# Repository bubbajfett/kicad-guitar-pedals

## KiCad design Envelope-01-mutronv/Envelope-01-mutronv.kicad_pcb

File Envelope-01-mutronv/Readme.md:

Envelope filter based on the Mutron V

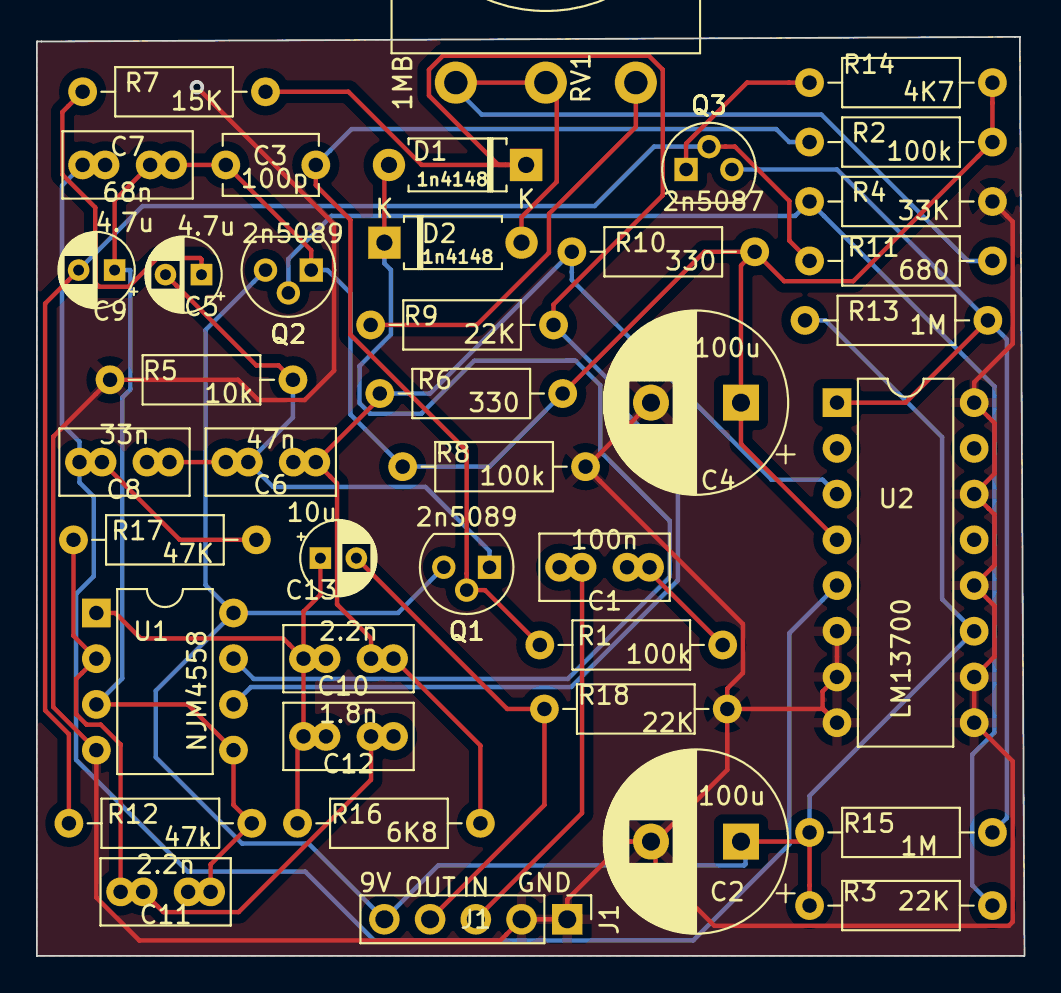
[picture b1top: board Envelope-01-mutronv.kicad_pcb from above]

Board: 2 copper layers, 54.9 x 51.1 mm, 40 parts (0 on the bottom side), 21 nets.

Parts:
C1: 100n; C_Rect_L7.0mm_W3.5mm_P2.50mm_P5.00mm
C2, C4: 100u; CP_Radial_D10.0mm_P5.00mm
C3: 100p; C_Disc_D5.1mm_W3.2mm_P5.00mm
C5, C9: 4.7u; CP_Radial_D4.0mm_P2.00mm
C6: 47n; C_Rect_L7.0mm_W3.5mm_P2.50mm_P5.00mm
C7: 68n; C_Rect_L7.0mm_W3.5mm_P2.50mm_P5.00mm
C8: 33n; C_Rect_L7.0mm_W3.5mm_P2.50mm_P5.00mm
C10, C11: 2.2n; C_Rect_L7.0mm_W3.5mm_P2.50mm_P5.00mm
C12: 1.8n; C_Rect_L7.0mm_W3.5mm_P2.50mm_P5.00mm
C13: 10u; CP_Radial_D4.0mm_P2.00mm
D1, D2: 1n4148; D_A-405_P7.62mm_Horizontal
J1: Conn_01x05; PinHeader_1x05_P2.54mm_Vertical
Q1, Q2: 2n5089; TO-92
Q3: 2n5087; TO-92
R1, R2, R8: 100k; R_Axial_DIN0207_L6.3mm_D2.5mm_P10.16mm_Horizontal
R3, R9, R18: 22K; R_Axial_DIN0207_L6.3mm_D2.5mm_P10.16mm_Horizontal
R4: 33K; R_Axial_DIN0207_L6.3mm_D2.5mm_P10.16mm_Horizontal
R5: 10k; R_Axial_DIN0207_L6.3mm_D2.5mm_P10.16mm_Horizontal
R6, R10: 330; R_Axial_DIN0207_L6.3mm_D2.5mm_P10.16mm_Horizontal
R7: 15K; R_Axial_DIN0207_L6.3mm_D2.5mm_P10.16mm_Horizontal
R11: 680; R_Axial_DIN0207_L6.3mm_D2.5mm_P10.16mm_Horizontal
R12: 47k; R_Axial_DIN0207_L6.3mm_D2.5mm_P10.16mm_Horizontal
R13, R15: 1M; R_Axial_DIN0207_L6.3mm_D2.5mm_P10.16mm_Horizontal
R14: 4K7; R_Axial_DIN0207_L6.3mm_D2.5mm_P10.16mm_Horizontal
R16: 6K8; R_Axial_DIN0207_L6.3mm_D2.5mm_P10.16mm_Horizontal
R17: 47K; R_Axial_DIN0207_L6.3mm_D2.5mm_P10.16mm_Horizontal
RV1: 1MB; Potentiometer_Omeg_PC16BU_Vertical
U1: NJM4558; DIP-8_W7.62mm
U2: LM13700; DIP-16_W7.62mm

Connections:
9v: C2.1, J1.5, Q1.3 (C), Q2.3 (C), R3.2, R13.2, R15.2, U1.8 (V+), U2.11 (V+)
GND: C2.2, C4.2, J1.1, J1.2, R4.1, R5.1, R8.1, R18.1, U1.4 (V-), U2.6 (V-), U2.7, U2.8, U2.9, U2.10, U2.12, U2.14 (+), U2.16
IN: C1.2, J1.3
unnamed: C1.1, R1.2
unnamed: C3.1, Q1.2 (B), R1.1, R2.2
unnamed: C5.1, R7.2
unnamed: C5.2, C6.2, C8.1, Q1.1 (E), R5.2
unnamed: C7.1, C8.2, R17.1, U2.5
unnamed: C9.2, Q3.2 (B), R11.2, R12.2
unnamed: C6.1, C10.1, R6.2, R10.2, R16.1, U2.3 (+)
unnamed: C10.2, C12.2, C13.1, R16.2, U1.1
unnamed: C11.2, C12.1, R17.2, U1.2 (-)
unnamed: D1.1 (K), R7.1, R9.1, U1.6 (-)
unnamed: D1.2 (A), D2.1 (K), U1.7
unnamed: Q2.2 (B), R3.1, R4.2
unnamed: Q3.1 (E), R14.2
unnamed: Q3.3 (C), R13.1, R15.1, U2.1
unnamed: R9.2, RV1.1
unnamed: D2.2 (A), R11.1, RV1.2, RV1.3
OUT: C13.2, J1.4, R18.2
VB: C3.2, C4.1, C7.2, C9.1, C11.1, Q2.1 (E), R2.1, R6.1, R8.2, R10.1, R12.1, R14.1, U1.3 (+), U1.5 (+), U2.4 (-)

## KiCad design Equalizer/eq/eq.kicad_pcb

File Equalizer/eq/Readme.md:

# eq

This is a 6-band equalizer based on a schematic in the PedalPCB site.
This is really a nice pedal to have on the board, and I like it in the
end of the chain, but not sure that is correct.   

All registered trademarks are owned by their respective owners.

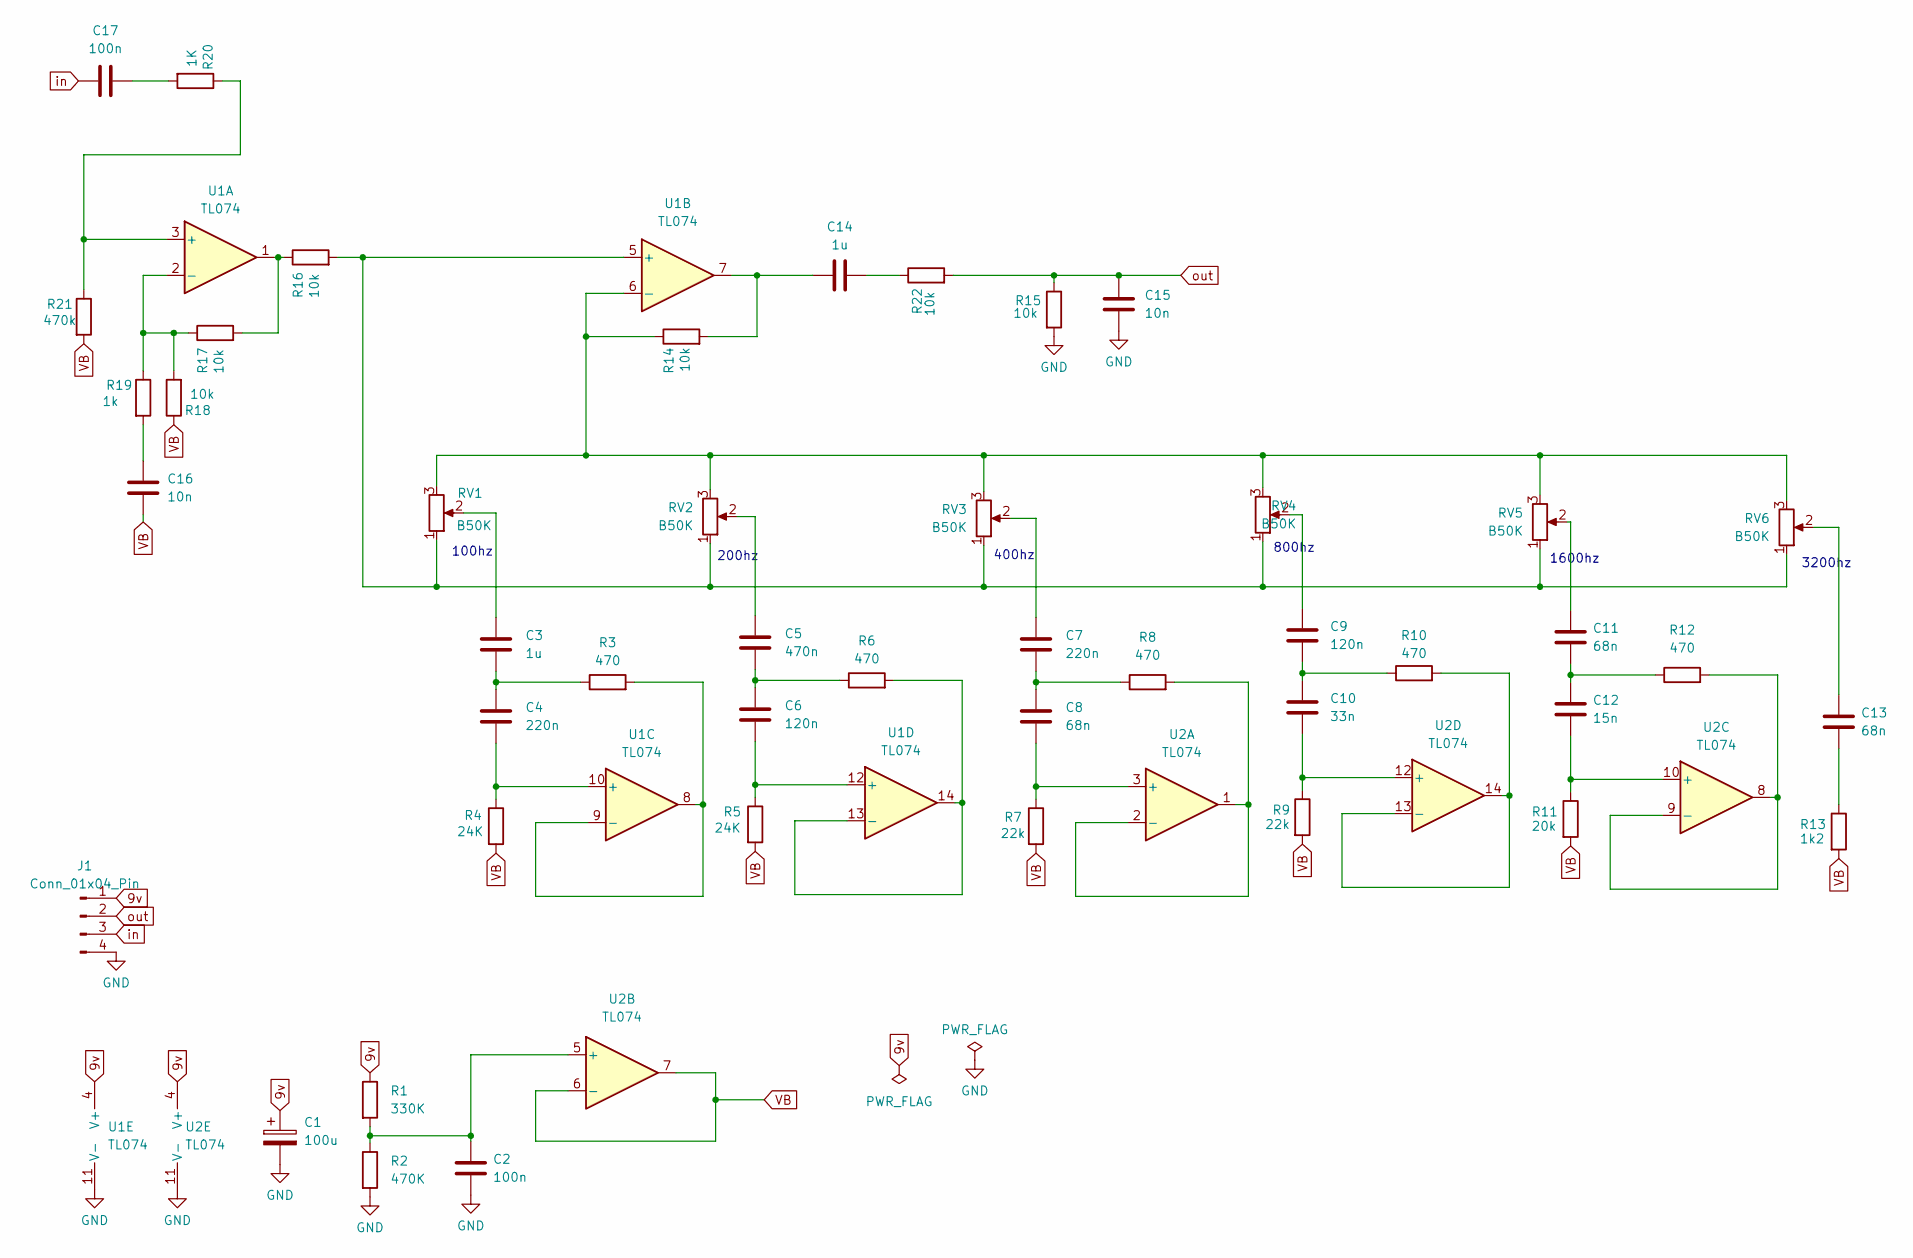
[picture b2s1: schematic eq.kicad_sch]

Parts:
C1: 100u; CP_Radial_D6.3mm_P2.50mm
C2, C17: 100n; C_Disc_D5.0mm_W2.5mm_P5.00mm
C3, C14: 1u; C_Disc_D5.0mm_W2.5mm_P5.00mm
C4, C7: 220n; C_Disc_D5.0mm_W2.5mm_P5.00mm
C5: 470n; C_Disc_D5.0mm_W2.5mm_P5.00mm
C6, C9: 120n; C_Disc_D5.0mm_W2.5mm_P5.00mm
C8, C11, C13: 68n; C_Disc_D5.0mm_W2.5mm_P5.00mm
C10: 33n; C_Disc_D5.0mm_W2.5mm_P5.00mm
C12: 15n; C_Disc_D5.0mm_W2.5mm_P5.00mm
C15, C16: 10n; C_Disc_D5.0mm_W2.5mm_P5.00mm
J1: Conn_01x04_Pin; PinHeader_1x04_P2.54mm_Vertical
R1: 330K; R_Axial_DIN0207_L6.3mm_D2.5mm_P7.62mm_Horizontal
R2: 470K; R_Axial_DIN0207_L6.3mm_D2.5mm_P7.62mm_Horizontal
R3, R6, R8, R10, R12: 470; R_Axial_DIN0207_L6.3mm_D2.5mm_P7.62mm_Horizontal
R4, R5: 24K; R_Axial_DIN0207_L6.3mm_D2.5mm_P7.62mm_Horizontal
R7, R9: 22k; R_Axial_DIN0207_L6.3mm_D2.5mm_P7.62mm_Horizontal
R11: 20k; R_Axial_DIN0207_L6.3mm_D2.5mm_P7.62mm_Horizontal
R13: 1k2; R_Axial_DIN0207_L6.3mm_D2.5mm_P7.62mm_Horizontal
R14, R15, R16, R17, R18, R22: 10k; R_Axial_DIN0207_L6.3mm_D2.5mm_P7.62mm_Horizontal
R19: 1k; R_Axial_DIN0207_L6.3mm_D2.5mm_P7.62mm_Horizontal
R20: 1K; R_Axial_DIN0207_L6.3mm_D2.5mm_P7.62mm_Horizontal
R21: 470k; R_Axial_DIN0207_L6.3mm_D2.5mm_P7.62mm_Horizontal
RV1, RV2, RV3, RV4, RV5, RV6: B50K; Potentiometer_Alps_RK09L_Single_Vertical
U1, U2: TL074; DIP-14_W7.62mm_LongPads

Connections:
9v: C1.1, J1.1, R1.1, U1.4 (V+), U2.4 (V+)
GND: C1.2, C2.2, C15.1, J1.4, R2.2, R15.2, U1.11 (V-), U2.11 (V-)
unnamed: C3.1, RV1.2
unnamed: C3.2, C4.1, R3.1
unnamed: C5.1, RV2.2
unnamed: C5.2, C6.1, R6.1
unnamed: C7.1, RV3.2
unnamed: C7.2, C8.1, R8.1
unnamed: C9.1, RV4.2
unnamed: C9.2, C10.1, R10.1
unnamed: C11.1, RV5.2
unnamed: C11.2, C12.1, R12.1
unnamed: C13.1, RV6.2
unnamed: C13.2, R13.1
unnamed: C14.1, R14.2, U1.7
unnamed: C14.2, R22.1
unnamed: C16.1, R19.2
unnamed: C17.1, R20.2
unnamed: R16.1, R17.2, U1.1
unnamed: R20.1, R21.1, U1.3 (+)
unnamed: R17.1, R18.2, R19.1, U1.2 (-)
unnamed: R16.2, RV1.1, RV2.1, RV3.1, RV4.1, RV5.1, RV6.1, U1.5 (+)
unnamed: R14.1, RV1.3, RV2.3, RV3.3, RV4.3, RV5.3, RV6.3, U1.6 (-)
unnamed: C4.2, R4.1, U1.10 (+)
unnamed: R3.2, U1.8, U1.9 (-)
unnamed: C6.2, R5.1, U1.12 (+)
unnamed: R6.2, U1.13 (-), U1.14
unnamed: C8.2, R7.1, U2.3 (+)
unnamed: R8.2, U2.1, U2.2 (-)
unnamed: C2.1, R1.2, R2.1, U2.5 (+)
unnamed: C12.2, R11.1, U2.10 (+)
unnamed: R12.2, U2.8, U2.9 (-)
unnamed: C10.2, R9.1, U2.12 (+)
unnamed: R10.2, U2.13 (-), U2.14
VB: C16.2, R4.2, R5.2, R7.2, R9.2, R11.2, R13.2, R18.1, R21.2, U2.6 (-), U2.7
in: C17.2, J1.3
out: C15.2, J1.2, R15.1, R22.2

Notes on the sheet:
800hz
1600hz
3200hz
100hz
400hz
200hz

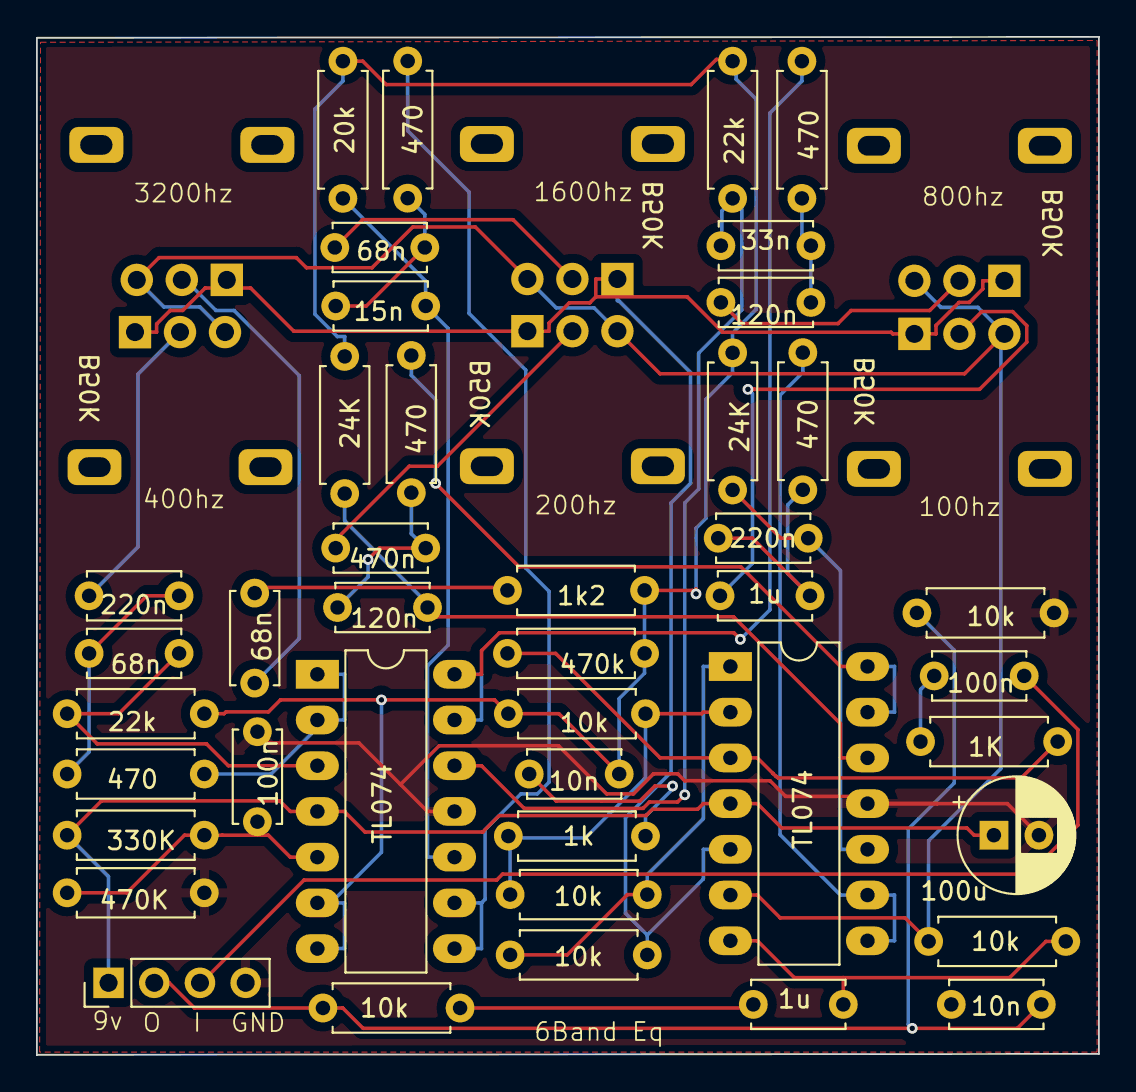
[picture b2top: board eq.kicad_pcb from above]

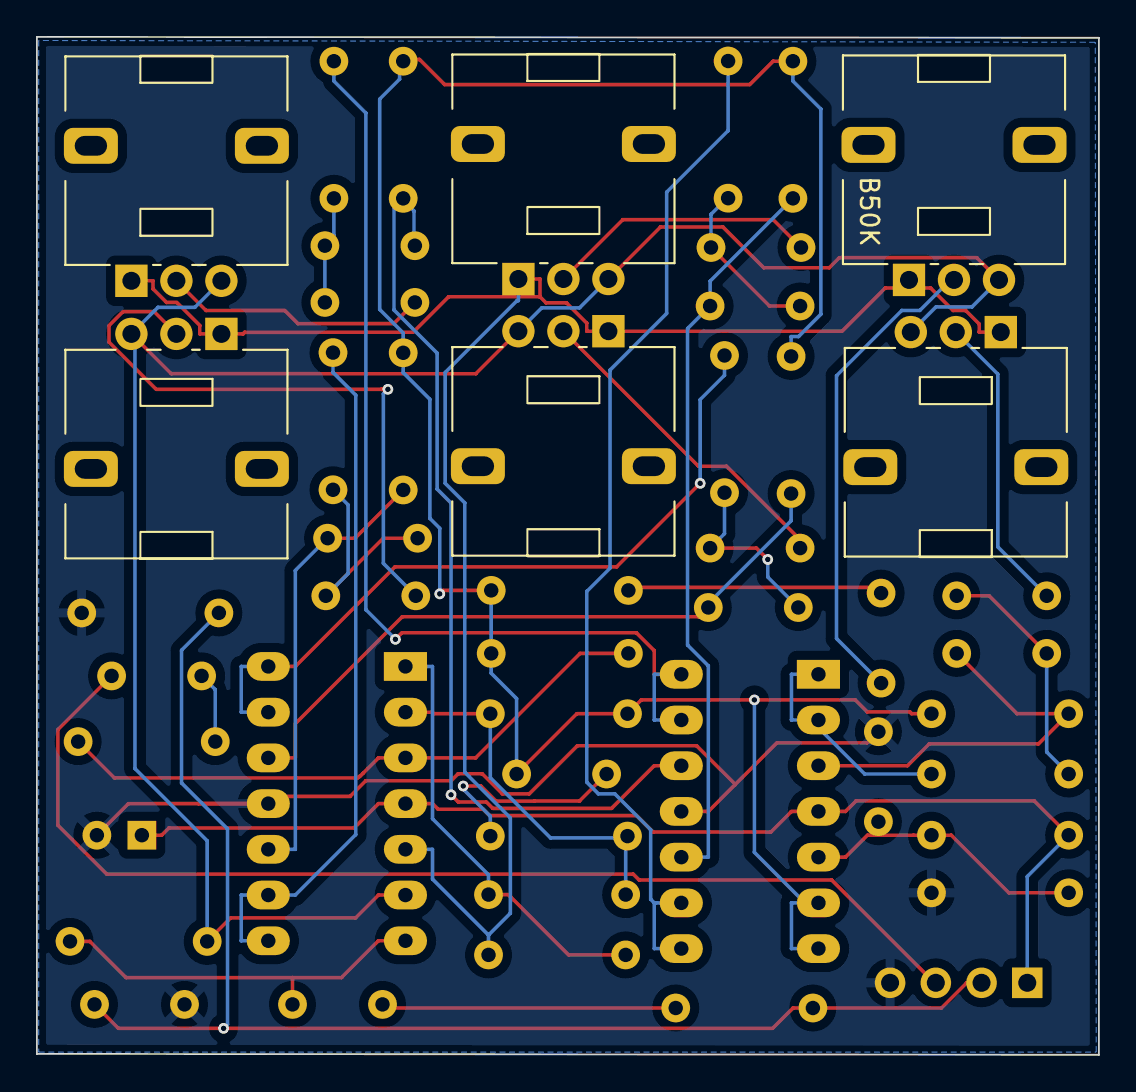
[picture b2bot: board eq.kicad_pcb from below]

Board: 2 copper layers, 59.0 x 56.5 mm, 48 parts (6 on the bottom side), 37 nets.

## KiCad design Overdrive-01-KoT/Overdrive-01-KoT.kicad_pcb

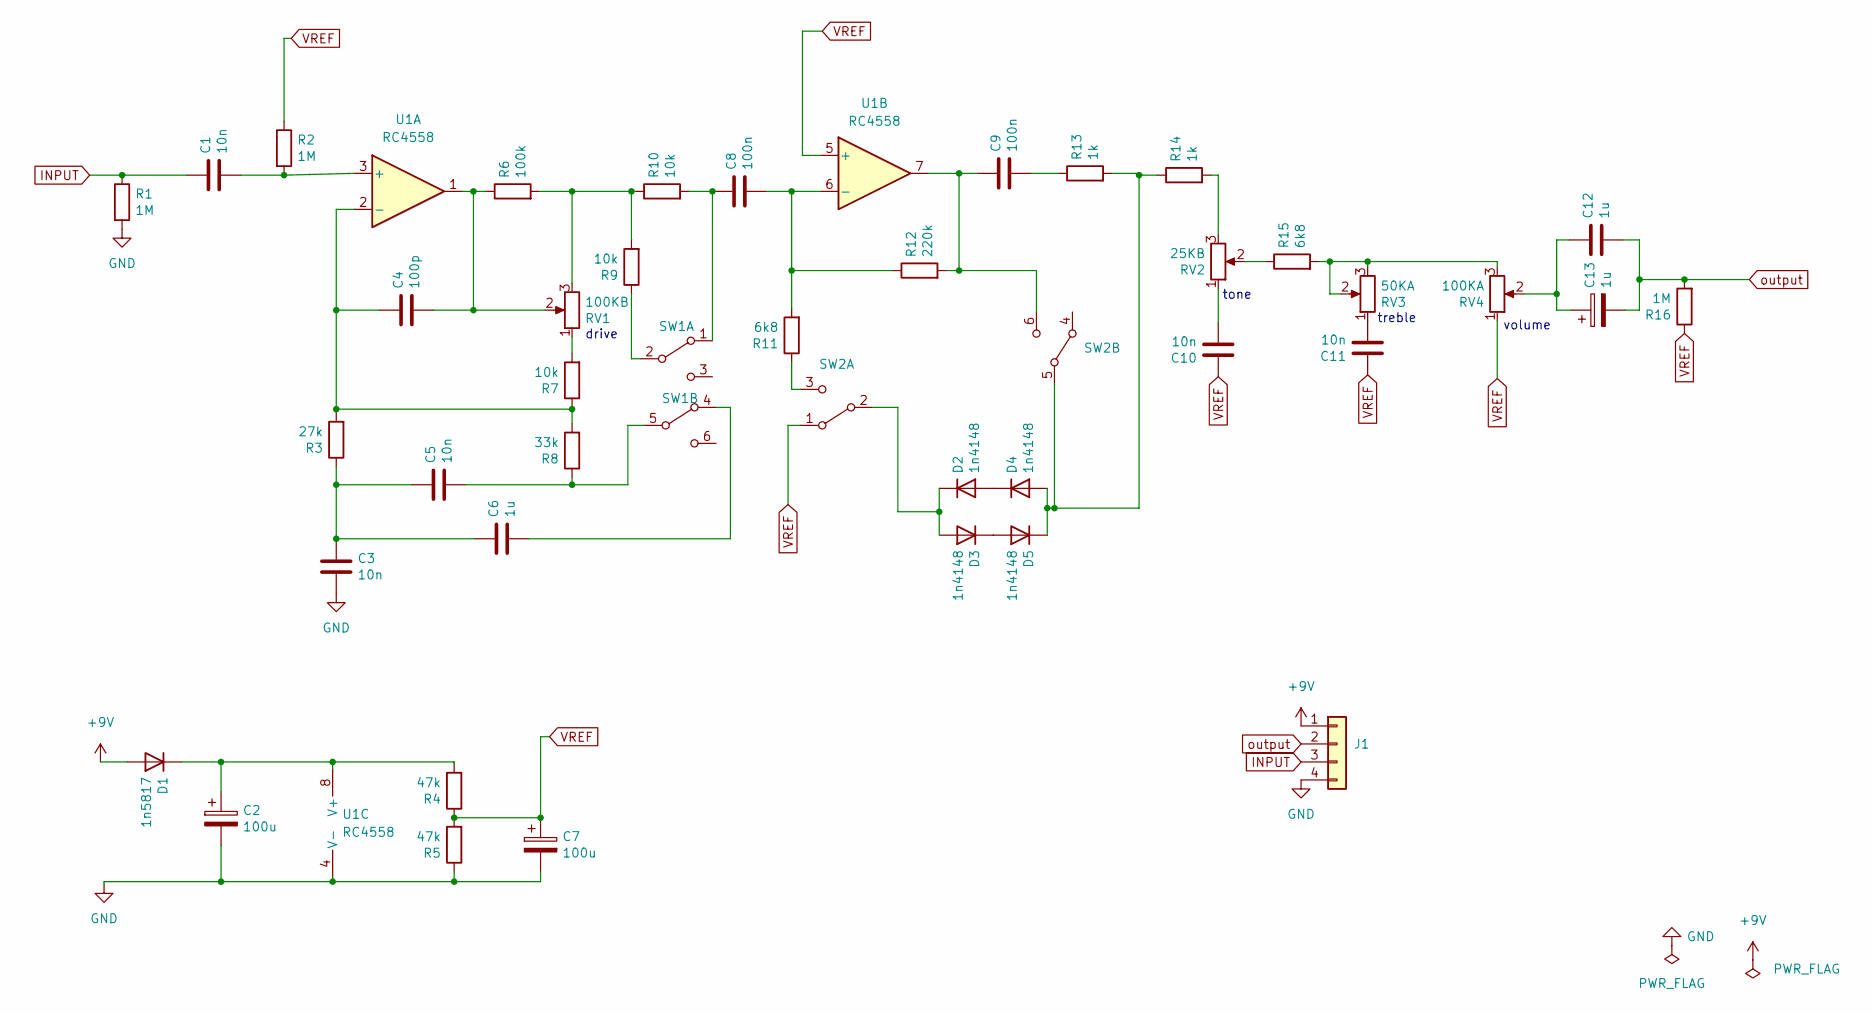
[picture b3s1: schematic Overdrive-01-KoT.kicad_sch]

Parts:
C1, C3, C5, C10: 10n; C_Disc_D5.0mm_W2.5mm_P5.00mm
C2, C7: 100u; CP_Radial_D6.3mm_P2.50mm
C4: 100p; C_Disc_D5.0mm_W2.5mm_P5.00mm
C6, C12: 1u; C_Disc_D5.0mm_W2.5mm_P5.00mm
C8, C9: 100n; C_Disc_D5.0mm_W2.5mm_P5.00mm
C11: 10n; C_Rect_L7.0mm_W2.5mm_P5.00mm
C13: 1u; CP_Radial_D6.3mm_P2.50mm
D1: 1n5817; D_A-405_P7.62mm_Horizontal
D2, D3, D4, D5: 1n4148; D_A-405_P7.62mm_Horizontal
J1: Conn_01x04; PinHeader_1x04_P2.54mm_Vertical
R1, R2, R16: 1M; R_Axial_DIN0207_L6.3mm_D2.5mm_P10.16mm_Horizontal
R3: 27k; R_Axial_DIN0207_L6.3mm_D2.5mm_P10.16mm_Horizontal
R4, R5: 47k; R_Axial_DIN0207_L6.3mm_D2.5mm_P10.16mm_Horizontal
R6: 100k; R_Axial_DIN0207_L6.3mm_D2.5mm_P10.16mm_Horizontal
R7, R9, R10: 10k; R_Axial_DIN0207_L6.3mm_D2.5mm_P10.16mm_Horizontal
R8: 33k; R_Axial_DIN0207_L6.3mm_D2.5mm_P10.16mm_Horizontal
R11, R15: 6k8; R_Axial_DIN0207_L6.3mm_D2.5mm_P10.16mm_Horizontal
R12: 220k; R_Axial_DIN0207_L6.3mm_D2.5mm_P10.16mm_Horizontal
R13, R14: 1k; R_Axial_DIN0207_L6.3mm_D2.5mm_P10.16mm_Horizontal
RV1: 100KB; 16MM_PCB_PADS
RV2: 25KB; 16MM_PCB_PADS
RV3: 50KA; 16MM_PCB_PADS
RV4: 100KA; 16MM_PCB_PADS
SW1: SW_DPST_x2; DPDTMini
SW2: SW_DPDT_x2; DPDTMini
U1: RC4558; DIP-8_W7.62mm_Socket

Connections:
+9V: D1.2 (A), J1.1
GND: C2.2, C3.2, C7.2, J1.4, R1.2, R5.1, U1.4 (V-)
INPUT: C1.1, J1.3, R1.1
unnamed: C1.2, R2.2, U1.3 (+)
unnamed: C2.1, D1.1 (K), R4.2, U1.8 (V+)
unnamed: C3.1, C5.1, C6.1, R3.1
unnamed: C4.1, R3.2, R7.1, R8.2, U1.2 (-)
unnamed: C4.2, R6.1, RV1.2, U1.1
unnamed: C5.2, R8.1, SW1.5 (B)
unnamed: C6.2, SW1.4 (A)
unnamed: C8.1, R10.2, SW1.1 (A)
unnamed: C8.2, R11.2, R12.1, U1.6 (-)
unnamed: C9.1, R12.2, SW2.6 (C), U1.7
unnamed: C9.2, R13.1
unnamed: C10.2, RV2.1
unnamed: C11.2, RV3.1
unnamed: C12.1, C13.1, RV4.2
unnamed: D2.1 (K), D3.2 (A), SW2.2 (B)
unnamed: D2.2 (A), D4.1 (K)
unnamed: D3.1 (K), D5.2 (A)
unnamed: D4.2 (A), D5.1 (K), R13.2, R14.1, SW2.5 (B)
unnamed: R7.2, RV1.1
unnamed: R9.1, SW1.2 (B)
unnamed: R6.2, R9.2, R10.1, RV1.3
unnamed: R11.1, SW2.3 (C)
unnamed: R14.2, RV2.3
unnamed: R15.1, RV2.2
unnamed: R15.2, RV3.2, RV3.3, RV4.3
VREF: C7.1, C10.1, C11.1, R2.1, R4.1, R5.2, R16.1, RV4.1, SW2.1 (A), U1.5 (+)
output: C12.2, C13.2, J1.2, R16.2

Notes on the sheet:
drive
volume
treble
tone

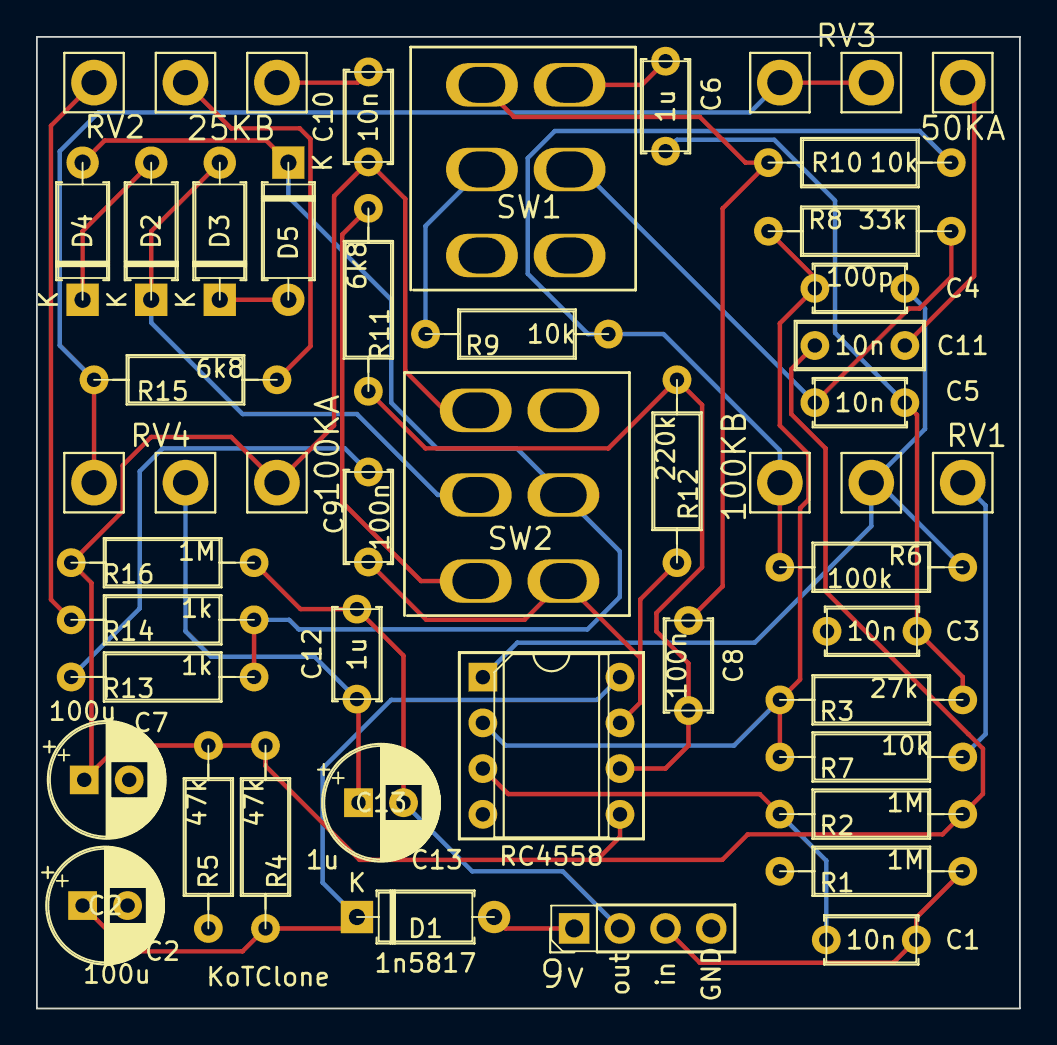
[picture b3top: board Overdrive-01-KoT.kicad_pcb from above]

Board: 2 copper layers, 54.6 x 54.0 mm, 42 parts (0 on the bottom side), 30 nets.

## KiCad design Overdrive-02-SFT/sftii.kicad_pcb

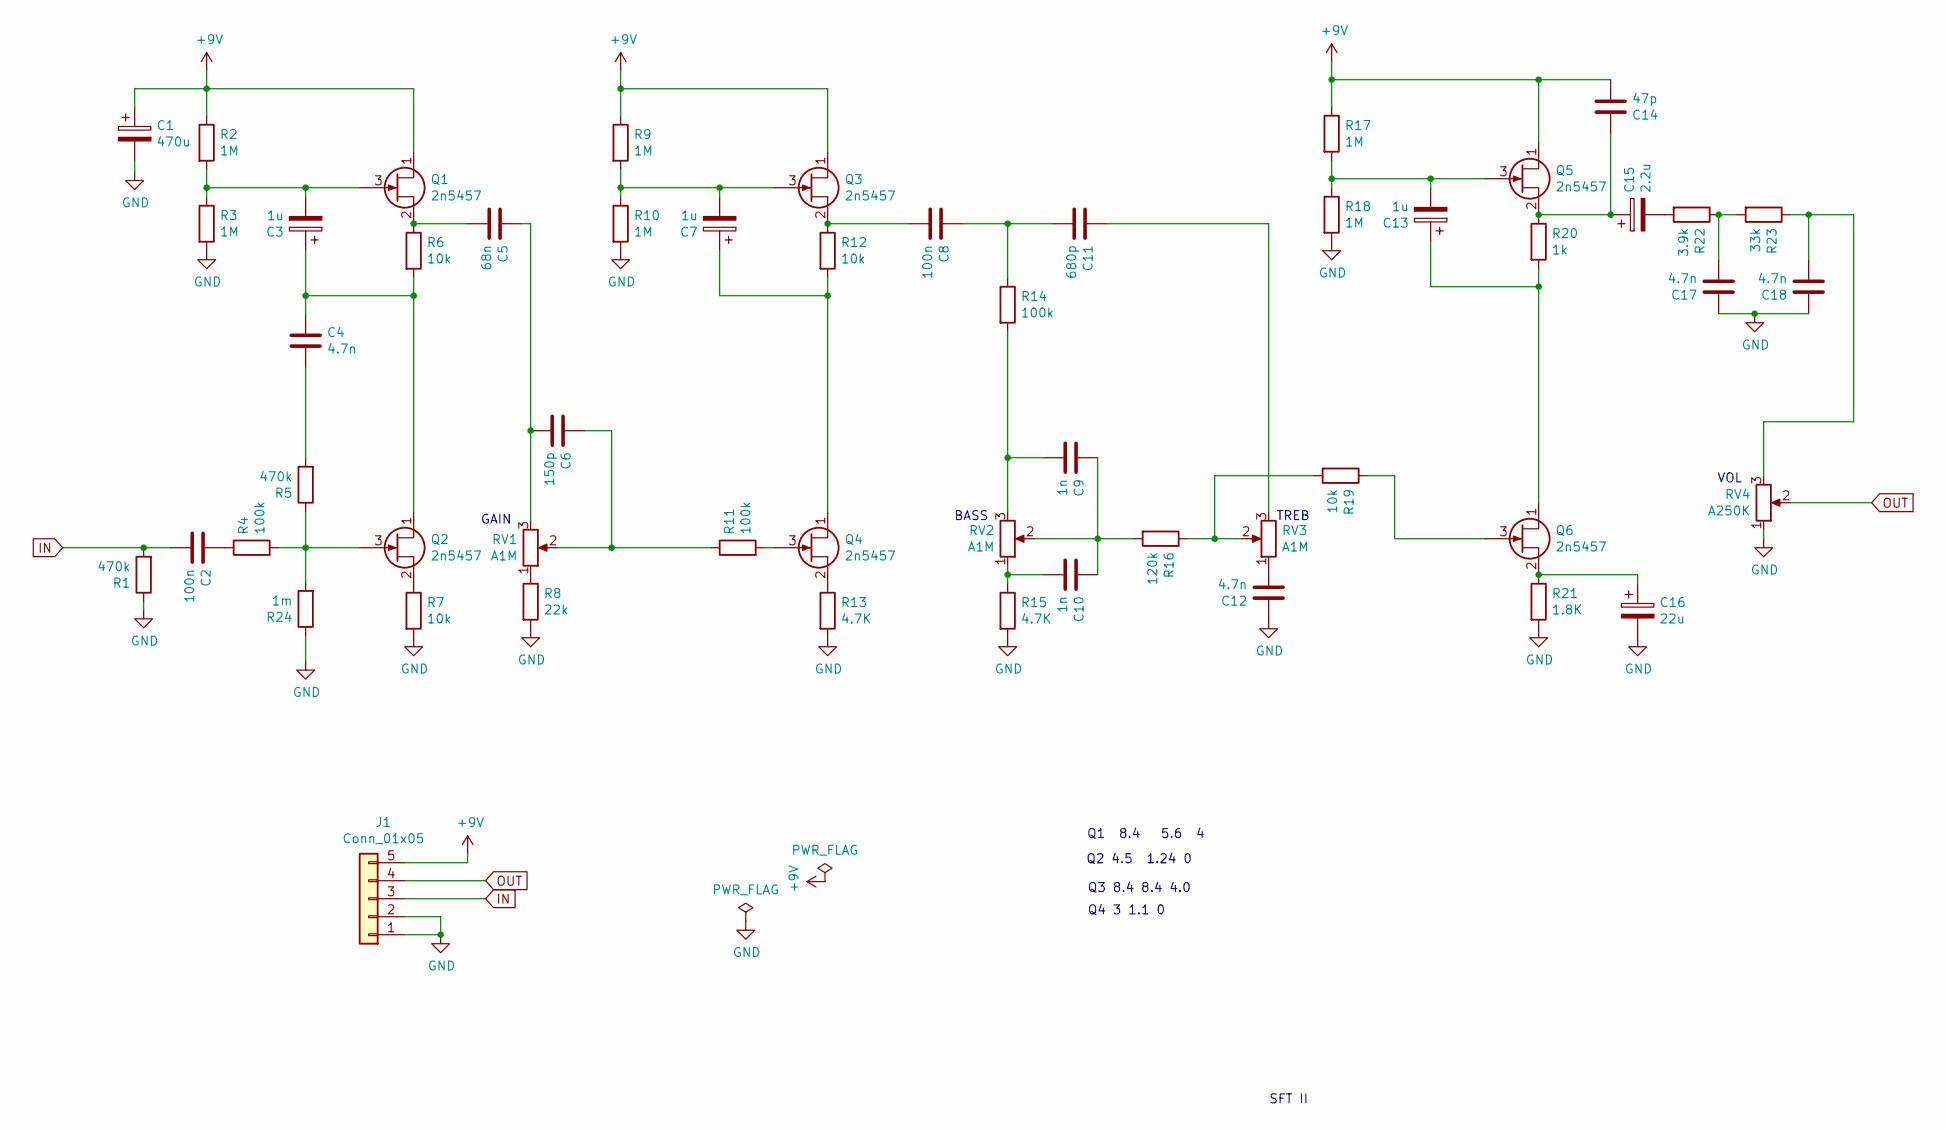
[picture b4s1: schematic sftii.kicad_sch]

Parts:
C1: 470u; CP_Radial_D8.0mm_P3.50mm
C2, C8: 100n; C_Rect_L7.0mm_W3.5mm_P5.00mm
C3, C7, C13: 1u; CP_Radial_D4.0mm_P2.00mm
C4, C12, C17, C18: 4.7n; C_Rect_L7.0mm_W3.5mm_P5.00mm
C5: 68n; C_Rect_L7.0mm_W3.5mm_P5.00mm
C6: 150p; C_Disc_D5.1mm_W3.2mm_P5.00mm
C9, C10: 1n; C_Rect_L7.0mm_W3.5mm_P5.00mm
C11: 680p; C_Disc_D5.0mm_W2.5mm_P5.00mm
C14: 47p; C_Disc_D5.1mm_W3.2mm_P5.00mm
C15: 2.2u; CP_Radial_D4.0mm_P2.00mm
C16: 22u; CP_Radial_D5.0mm_P2.00mm
J1: Conn_01x05; PinHeader_1x05_P2.54mm_Vertical
Q1, Q2, Q3, Q4, Q5, Q6: 2n5457; TO-92_HandSolder
R1, R5: 470k; R_Axial_DIN0207_L6.3mm_D2.5mm_P10.16mm_Horizontal
R2, R3, R9, R10, R17, R18: 1M; R_Axial_DIN0207_L6.3mm_D2.5mm_P10.16mm_Horizontal
R4, R11, R14: 100k; R_Axial_DIN0207_L6.3mm_D2.5mm_P10.16mm_Horizontal
R6, R7, R12, R19: 10k; R_Axial_DIN0207_L6.3mm_D2.5mm_P10.16mm_Horizontal
R8: 22k; R_Axial_DIN0207_L6.3mm_D2.5mm_P10.16mm_Horizontal
R13, R15: 4.7K; R_Axial_DIN0207_L6.3mm_D2.5mm_P10.16mm_Horizontal
R16: 120k; R_Axial_DIN0207_L6.3mm_D2.5mm_P10.16mm_Horizontal
R20: 1k; R_Axial_DIN0207_L6.3mm_D2.5mm_P10.16mm_Horizontal
R21: 1.8K; R_Axial_DIN0207_L6.3mm_D2.5mm_P10.16mm_Horizontal
R22: 3.9k; R_Axial_DIN0207_L6.3mm_D2.5mm_P10.16mm_Horizontal
R23: 33k; R_Axial_DIN0207_L6.3mm_D2.5mm_P10.16mm_Horizontal
R24: 1m; R_Axial_DIN0207_L6.3mm_D2.5mm_P10.16mm_Horizontal
RV1, RV2, RV3: A1M; Pot_Underside
RV4: A250K; Pot_Underside

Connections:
+9V: C1.1, C14.2, J1.5, Q1.1 (D), Q3.1 (D), Q5.1 (D), R2.1, R9.1, R17.1
GND: C1.2, C12.1, C16.2, C17.1, C18.1, J1.1, J1.2, R1.1, R3.2, R7.2, R8.2, R10.2, R13.2, R15.2, R18.2, R21.2, R24.1, RV4.1
IN: C2.2, J1.3, R1.2
unnamed: C2.1, R4.1
unnamed: C4.2, R5.2
unnamed: C5.1, C6.2, RV1.3
unnamed: C6.1, R11.1, RV1.2
unnamed: C9.2, R14.2, RV2.3
unnamed: C9.1, C10.1, R16.2, RV2.2
unnamed: C10.2, R15.1, RV2.1
unnamed: C11.1, RV3.3
unnamed: C8.1, C11.2, R14.1
unnamed: C12.2, RV3.1
unnamed: C15.2, R22.2
unnamed: C17.2, R22.1, R23.2
unnamed: C18.2, R23.1, RV4.3
unnamed: C3.2, Q1.3 (G), R2.2, R3.1
unnamed: C5.2, Q1.2 (S), R6.1
unnamed: C3.1, C4.1, Q2.1 (D), R6.2
unnamed: Q2.3 (G), R4.2, R5.1, R24.2
unnamed: Q2.2 (S), R7.1
unnamed: C7.2, Q3.3 (G), R9.2, R10.1
unnamed: C8.2, Q3.2 (S), R12.1
unnamed: C7.1, Q4.1 (D), R12.2
unnamed: Q4.3 (G), R11.2
unnamed: Q4.2 (S), R13.1
unnamed: C13.2, Q5.3 (G), R17.2, R18.1
unnamed: C14.1, C15.1, Q5.2 (S), R20.1
unnamed: C13.1, Q6.1 (D), R20.2
unnamed: Q6.3 (G), R19.1
unnamed: C16.1, Q6.2 (S), R21.1
unnamed: R8.1, RV1.1
unnamed: R16.1, R19.2, RV3.2
OUT: J1.4, RV4.2

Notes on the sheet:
Q4 3 1.1 0
Q1 8.4 5.6 4
BASS
TREB
Q2 4.5 1.24 0
Q3 8.4 8.4 4.0
GAIN
SFT II
VOL

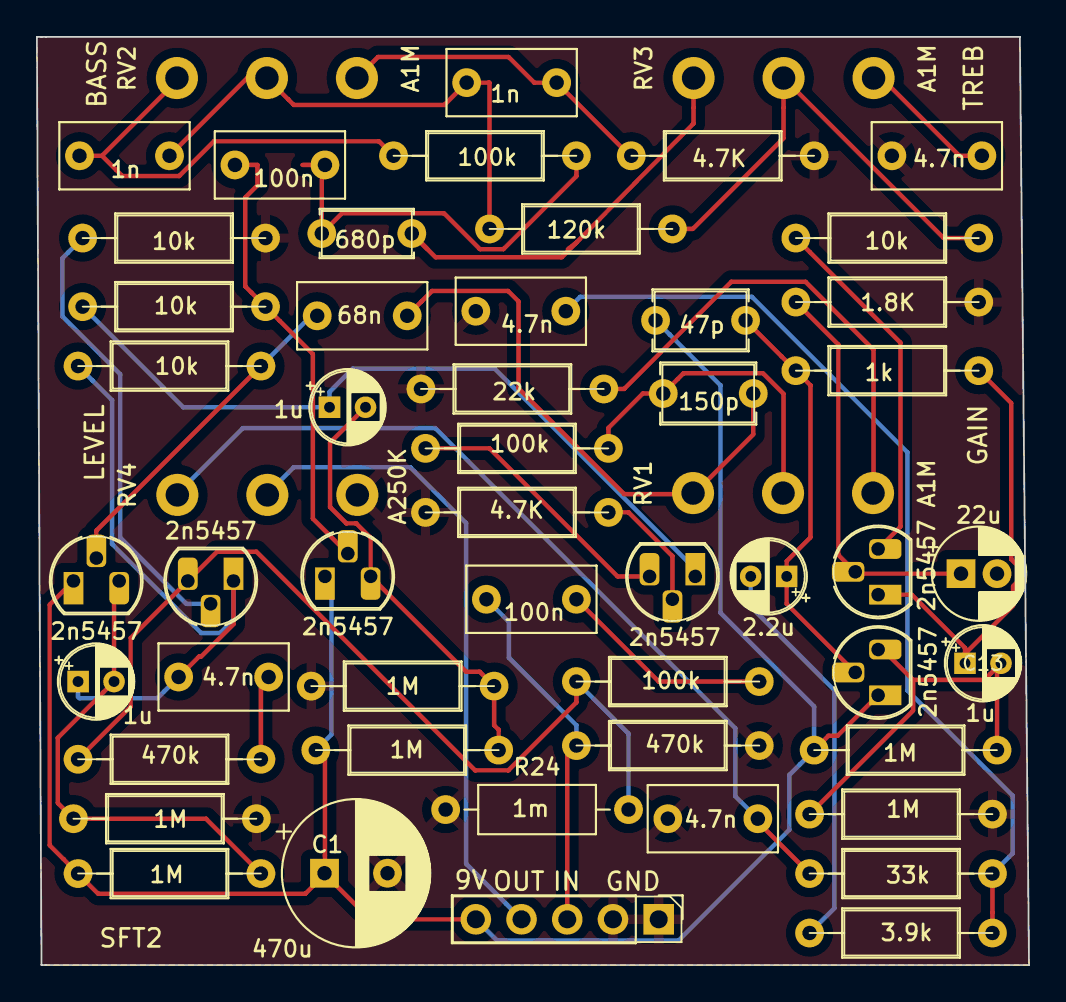
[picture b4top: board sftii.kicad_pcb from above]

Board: 2 copper layers, 55.1 x 51.6 mm, 53 parts (0 on the bottom side), 34 nets.

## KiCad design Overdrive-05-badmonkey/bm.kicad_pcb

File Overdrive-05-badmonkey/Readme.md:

# badmonkey

This is a clone of the digitech Bad Monkey overdrive.   This is apparently
a derivative of the tubescreamer pedal from some time ago.   This uses
a gyrator circut for the low's.

Very nice sound.

This is the 2nd version of the pedal.   The first version was missing
the R15/C12.    This was added to the first version of the pedal as a bodge.

So this pedal is verified. I have not boxed this one yet, either.

All trademarks belong to their respective owners.

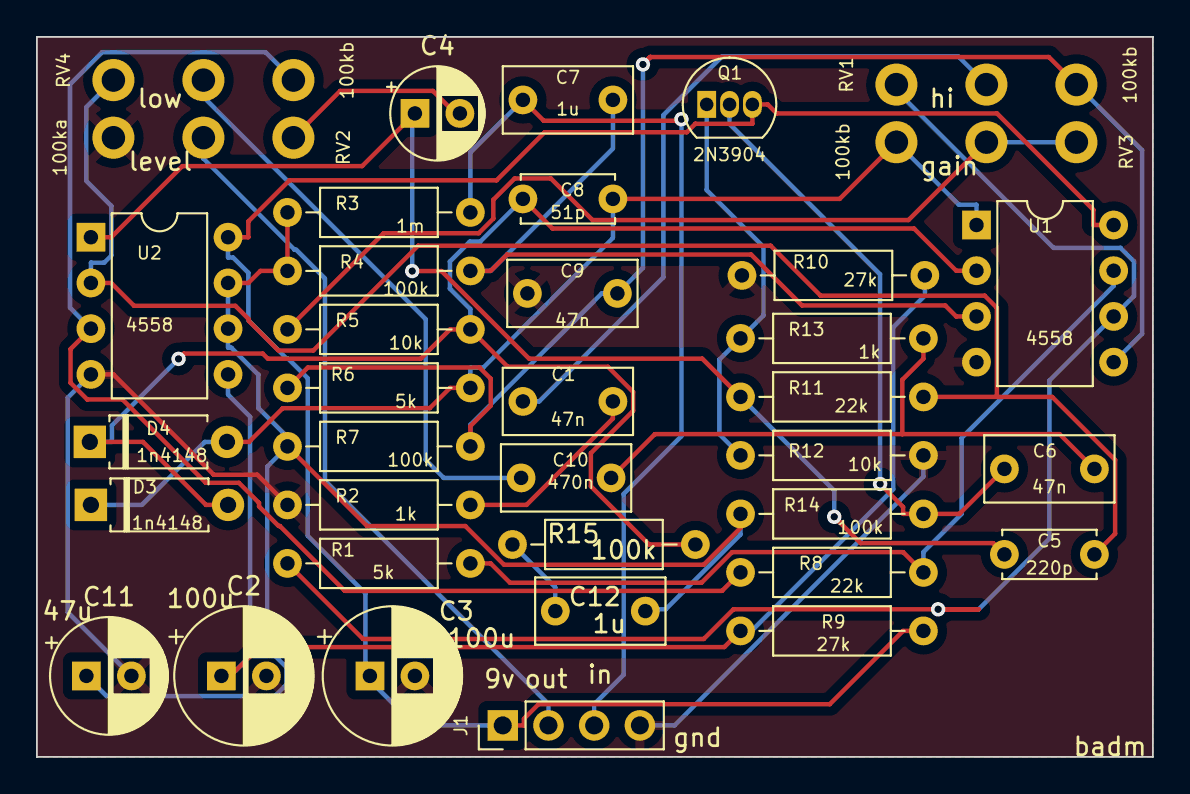
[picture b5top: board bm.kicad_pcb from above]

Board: 2 copper layers, 62.0 x 40.0 mm, 37 parts (0 on the bottom side), 24 nets.

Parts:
C1, C6, C9: 47n; C_Rect_L7.0mm_W3.5mm_P5.00mm
C2, C3: 100u; CP_Radial_D7.5mm_P2.50mm
C4: 10u; CP_Radial_D5.0mm_P2.50mm
C5: 220p; C_Disc_D5.0mm_W2.5mm_P5.00mm
C7, C12: 1u; C_Rect_L7.0mm_W3.5mm_P5.00mm
C8: 51p; C_Disc_D5.0mm_W2.5mm_P5.00mm
C10: 470n; C_Rect_L7.0mm_W3.5mm_P5.00mm
C11: 47u; CP_Radial_D6.3mm_P2.50mm
D3, D4: 1n4148; D_A-405_P7.62mm_Horizontal
J1: Conn_01x04_Pin; PinHeader_1x04_P2.54mm_Vertical
Q1: 2N3904; TO-92_Inline
R1, R6: 5k; R_Axial_DIN0207_L6.3mm_D2.5mm_P10.16mm_Horizontal
R2, R13: 1k; R_Axial_DIN0207_L6.3mm_D2.5mm_P10.16mm_Horizontal
R3: 1m; R_Axial_DIN0207_L6.3mm_D2.5mm_P10.16mm_Horizontal
R4, R7, R14, R15: 100k; R_Axial_DIN0207_L6.3mm_D2.5mm_P10.16mm_Horizontal
R5, R12: 10k; R_Axial_DIN0207_L6.3mm_D2.5mm_P10.16mm_Horizontal
R8, R11: 22k; R_Axial_DIN0207_L6.3mm_D2.5mm_P10.16mm_Horizontal
R9, R10: 27k; R_Axial_DIN0207_L6.3mm_D2.5mm_P10.16mm_Horizontal
RV1, RV3, RV4: 100kb; Pot_Underside
RV2: 100ka; Pot_Underside
U1, U2: 4558; DIP-8_W7.62mm

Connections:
+9V: C3.1, J1.1, Q1.3 (C), R9.2, U1.8 (V+), U2.8 (V+)
GND: C2.2, C3.2, C9.1, C11.2, J1.4, R2.1, R10.1, R12.2, RV2.1, U1.4 (V-), U2.4 (V-)
IN: C7.1, J1.3, R3.2
unnamed: C1.1, RV1.2
unnamed: C1.2, R2.2
unnamed: C4.1, C5.2, R11.1, U2.1
unnamed: C4.2, RV2.3
unnamed: C10.1, RV4.2
unnamed: C6.2, C10.2, R13.2
unnamed: C12.2, R15.1
unnamed: C8.1, D3.2 (A), D4.1 (K), R5.2, R15.2, U1.2 (-)
unnamed: C8.2, D3.1 (K), D4.2 (A), R6.2, RV3.1, U1.1
unnamed: C6.1, Q1.2 (B), R14.2
unnamed: Q1.1 (E), R12.1, R13.1
unnamed: R1.2, R8.2, U1.7
unnamed: R5.1, RV3.2, RV3.3
unnamed: C7.2, R4.2, U1.3 (+)
unnamed: C9.2, R6.1, R7.2, RV1.1, U1.5 (+)
unnamed: R1.1, RV1.3, U1.6 (-)
unnamed: R8.1, RV4.1, U2.3 (+)
unnamed: C5.1, R11.2, RV4.3, U2.2 (-)
unnamed: C2.1, R9.1, R10.2, U2.5 (+)
out: J1.2, RV2.2
vb: C11.1, C12.1, R3.1, R4.1, R7.1, R14.1, U2.6 (-), U2.7
